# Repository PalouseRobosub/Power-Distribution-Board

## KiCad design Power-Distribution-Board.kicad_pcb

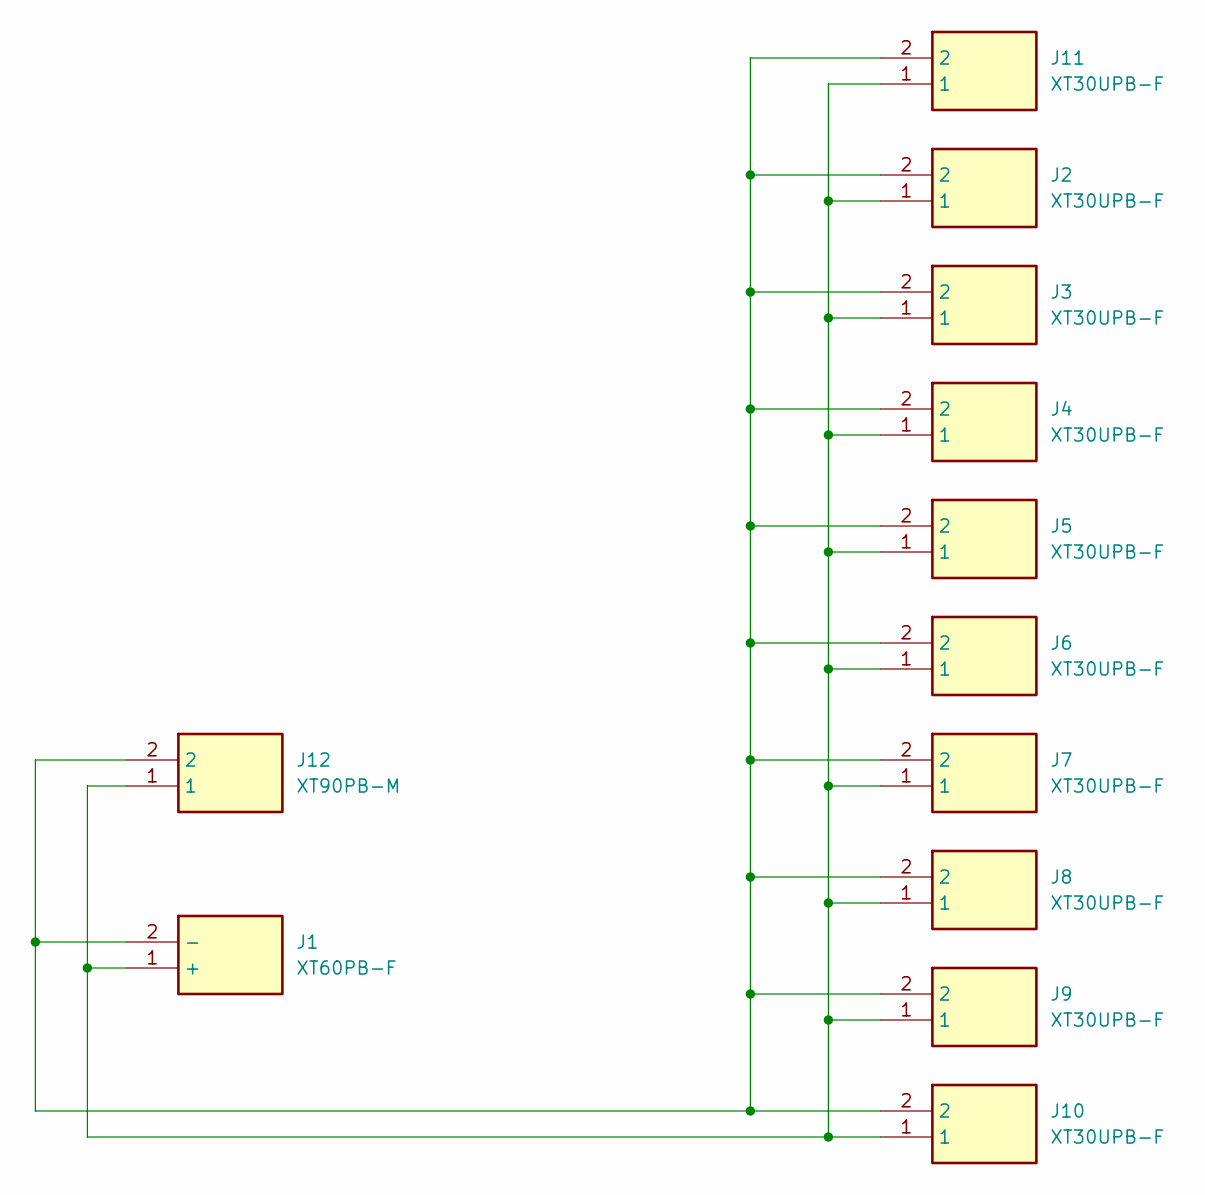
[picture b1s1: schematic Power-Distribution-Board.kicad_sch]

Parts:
J1: XT60PB-F; XT60PBF; Manufacturer_Part_Number XT60PB-F
J2, J3, J4, J5, J6, J7, J8, J9, J10, J11: XT30UPB-F; XT30UPBF; Manufacturer_Part_Number XT30UPB-F
J12: XT90PB-M; XT90PBM; Manufacturer_Part_Number XT90PB-M

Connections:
unnamed: J1.1 (+), J2.1, J3.1, J4.1, J5.1, J6.1, J7.1, J8.1, J9.1, J10.1, J11.1, J12.1
unnamed: J1.2 (-), J2.2, J3.2, J4.2, J5.2, J6.2, J7.2, J8.2, J9.2, J10.2, J11.2, J12.2

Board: 2 copper layers, 12 parts (0 on the bottom side), 2 nets, no tracks yet.

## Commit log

2026-01-13 Initial Commit
    Blank KiCad 9.0 project
2026-01-15 Added symbols for connectors
    XT30-F, XT60-F, XT90-M
2026-01-15 Reformatted library
2026-01-15 Set up footprints (probably incorrectly)
2026-01-15 Symbols should be fixed now
2026-01-15 Added models to connectors, changed XT90PB-F to -M
2026-01-15 Started Schematic and PCB layout
    Life is pain, I hate-
2026-01-15 Pressed B
2026-01-15 small update
    not enough town in this room for the two of us
2026-01-16 WIP updating size
2026-01-16 XT90 fully transitioned to male
2026-01-16 Circuit "the long way"
    how I like my peanut butter jelly
2026-01-16 Actually properly finally fixed the model
2026-01-17 the long way (wholesome)
    better PB and J
2026-01-18 stout board
2026-01-28 Added screw holes and measurements
